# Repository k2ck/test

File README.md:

View this project on [CADLAB.io](https://cadlab.io/project/1768). 

# test

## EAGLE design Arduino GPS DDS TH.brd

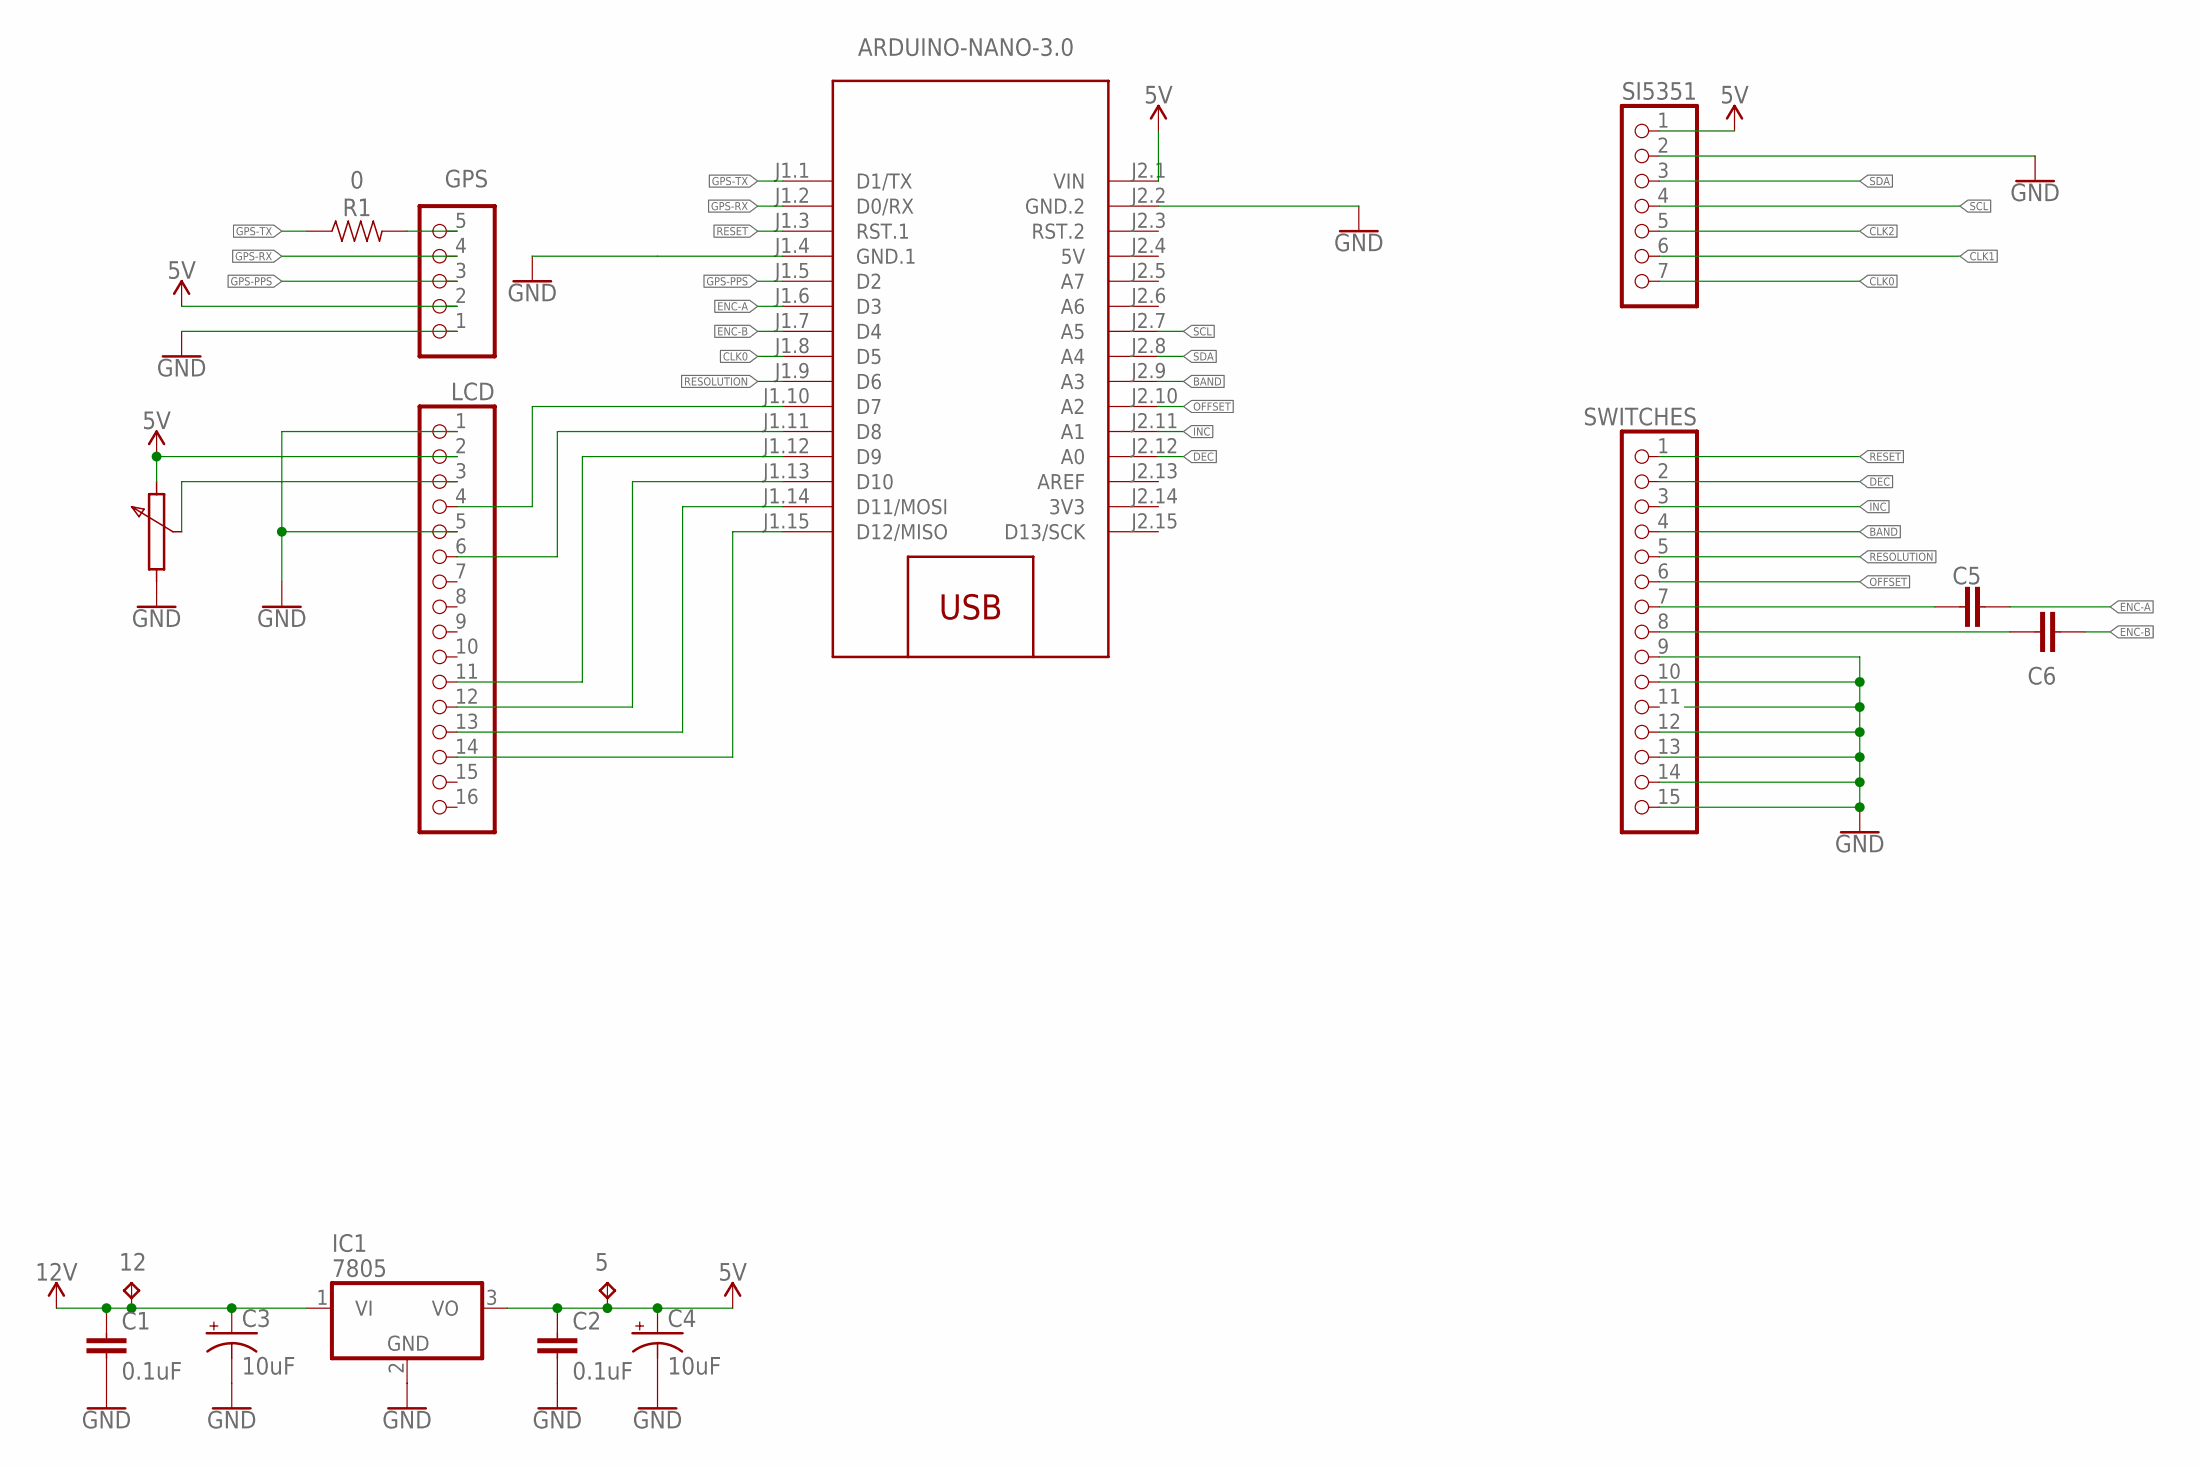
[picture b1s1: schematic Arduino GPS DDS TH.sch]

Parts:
5, 12: TPTP06R; TP06R
C1, C2, C5, C6: 0.1uF; CAP-PTH-SMALL-KIT
C3, C4: 10uF; CPOL-RADIAL-2.5MM-5MM-KIT
GPS: PINHD-1X5; 1X05
IC1: 7805; TO220V
LCD: PINHD-1X16; 1X16
M1: ARDUINO-NANO-3.0
R1: 0; AXIAL-0.3
SI5351: PINHD-1X7; 1X07
SWITCHES: PINHD-1X15; 1X15

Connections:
3V3: M1.J2.14 (3V3)
5V: M1.J2.4 (5V)
BAND: M1.J2.9 (A3), SWITCHES.4
CLK0: M1.J1.8 (D5), SI5351.7
CLK1: SI5351.6
CLK2: SI5351.5
DEC: M1.J2.12 (A0), SWITCHES.2
ENC-A: C5.2, M1.J1.6 (D3)
ENC-B: C6.2, M1.J1.7 (D4)
GND: C1.2, C2.2, C3.2 (-), C4.2 (-), GPS.1, IC1.2 (GND), LCD.1, LCD.5, M1.J1.4 (GND.1), M1.J2.2 (GND.2), SI5351.2, SWITCHES.9, SWITCHES.10, SWITCHES.12, SWITCHES.13, SWITCHES.14, SWITCHES.15
GPS-PPS: GPS.3, M1.J1.5 (D2)
GPS-RX: GPS.4, M1.J1.2 (D0/RX)
GPS-TX: M1.J1.1 (D1/TX), R1.P$1 (1)
INC: M1.J2.11 (A1), SWITCHES.3
unnamed: C5.1, SWITCHES.7
unnamed: C6.1, SWITCHES.8
unnamed: GPS.5, R1.P$2 (2)
unnamed: LCD.4, M1.J1.10 (D7)
unnamed: LCD.6, M1.J1.11 (D8)
unnamed: LCD.11, M1.J1.12 (D9)
unnamed: LCD.12, M1.J1.13 (D10)
unnamed: LCD.13, M1.J1.14 (D11/MOSI)
unnamed: LCD.14, M1.J1.15 (D12/MISO)
OFFSET: M1.J2.10 (A2), SWITCHES.6
RESET: M1.J1.3 (RST.1), SWITCHES.1
RESOLUTION: M1.J1.9 (D6), SWITCHES.5
SCL: M1.J2.7 (A5), SI5351.4
SDA: M1.J2.8 (A4), SI5351.3
VCC_1: 12.TP, C1.1, C3.1 (+), IC1.1 (VI)
VCC_2: 5.TP, C2.1, C4.1 (+), GPS.2, IC1.3 (VO), LCD.2, M1.J2.1 (VIN), SI5351.1

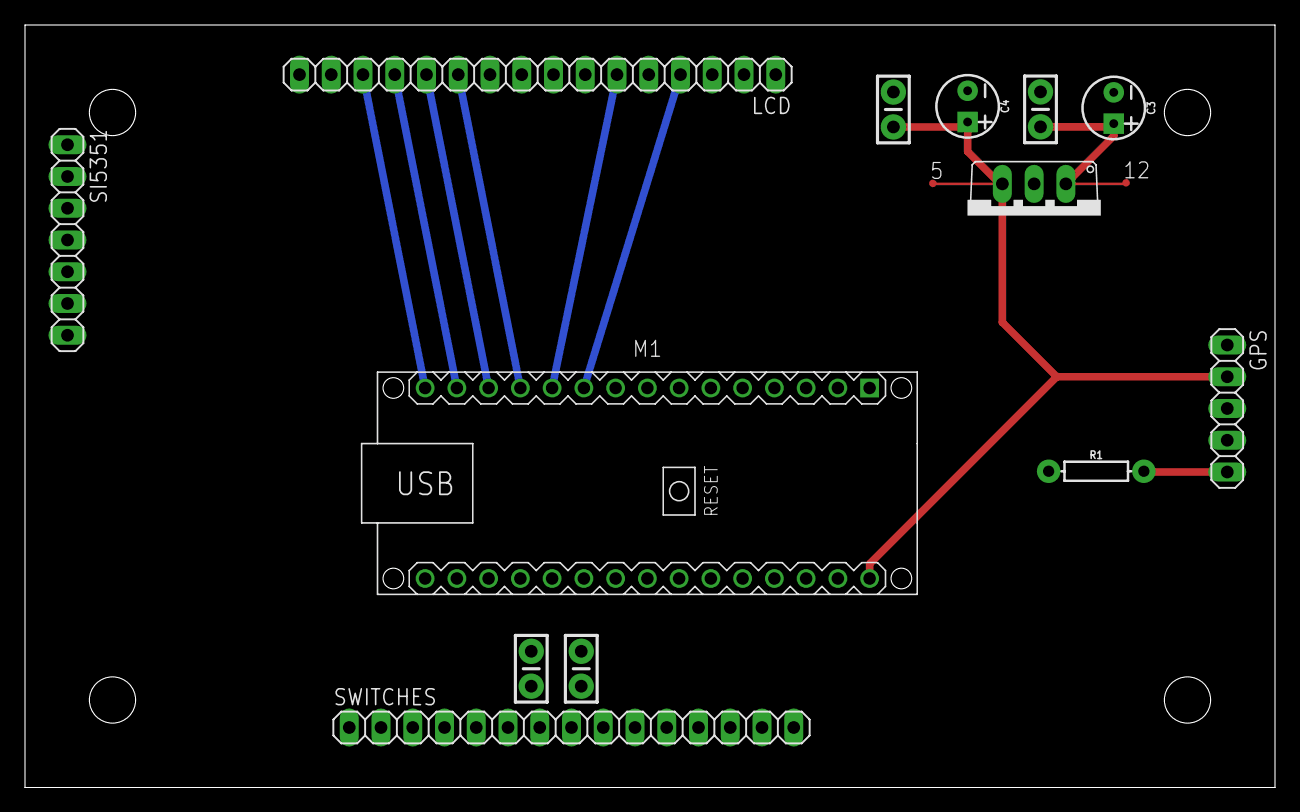
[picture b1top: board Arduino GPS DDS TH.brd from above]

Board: 2 copper layers, 100.0 x 61.0 mm, 15 parts (0 on the bottom side), 26 nets.

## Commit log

2019-05-13 Backlink to CADLAB.io has been added.
2019-05-13 Update
    Added diode to design

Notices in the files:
parts and their libraries:
SparkFun-Capacitors: Licensing: Creative Commons ShareAlike 4.0 International - https://creativecommons.org/licenses/by-sa/4.0
diy-modules: Released under the Creative Commons Attribution 4.0 International License: http://creativecommons.org/licenses/by/4.0
